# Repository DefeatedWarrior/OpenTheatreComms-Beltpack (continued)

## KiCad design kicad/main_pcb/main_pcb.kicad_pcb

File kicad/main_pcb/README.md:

# Beltpack main PCB, rev 0.1

The board behind the front shell: USB-C charging with a power path, the soft power switch and 3.3 V LDO, a fuel gauge,
the ESP32-S3 module, the LR2021 radio module with its antenna-diversity switch and two U.FL outputs, the NAU88C22 codec
with the XLR-4 headset and 3.5 mm TRRS outputs, an accelerometer, an IO expander, the three front buttons, the
flashlight LED, the vibration motor and the JST SH link to the top PCB.

| | |
|---|---|
| Size | 87.5 x 64.5 mm outline with the link tab, 1.6 mm FR4, 4 layers |
| Stack | F signal + GND pour, In1 signal + +3V3 pour, In2 solid GND plane, B signal + GND pour |
| Rules | 0.2 mm track and space, power and +3V3 0.4 mm, RF 0.35 mm, vias 0.6 / 0.3 mm, 0.5 mm copper to edge |
| Parts | 138 parts (59 on the front, 79 on the back; 21 of them unfitted options) plus 5 M2 holes. 0603 passives on hand-solder pads |
| DRC | 0 errors, 0 unconnected. 10 warnings, all expected: footprints adjusted from their library copies (silk moved off the board edge), the enclosure reference footprint has no library, and one pin-1 marker clipped by the mask |

## Files

| Path | Contents |
|---|---|
| `main_pcb.kicad_sch` | Schematic (one A1 sheet, a box per block) |
| `main_pcb.kicad_pcb` | Routed board. *Update PCB from Schematic* matches every footprint to its symbol |
| `main_pcb.kicad_dru` | Custom rules: single thermal spoke, the USB-C and power-switch pegs, the buttons by the tab edge |
| `lib/` | Project symbols and footprints (codec, charger, gauge, RF switch, LR2021 module, spring pin, coin motor) |
| `fab/main_pcb_gerbers.zip` | Gerbers (4 copper layers) + Excellon drill (PTH and NPTH), ready to upload |
| `fab/main_pcb_bom.csv` | BOM grouped by value, with part numbers and side. Unfitted parts are listed with quantity 0 |
| `fab/main_pcb_placement.csv` | Pick-and-place, mm (unfitted parts left out) |
| `fab/assembly.pdf` | Hand-assembly sheets, front and back (back drawn as seen from the back); unfitted parts in grey |
| `fab/main_pcb_schematic.pdf`, `fab/main_pcb_drc.rpt` | Schematic print and the DRC report |

Order as: 4 layers, 1.6 mm, JLC-style 7628 stack (or any 4-layer stack with about 0.2 mm from B to In2: the RF lines
were sized for that), HASL lead-free is fine for reflow (ENIG gives a flatter paste print on the QFN, TDFN and LGA, if you want the margin), any mask colour. The ESP32 and codec footprints have
0.2 mm thermal vias, so allow 0.2 mm drills.

## Circuit

**Power.** USB-C (5.1k CC pull-downs, so it asks for 5 V only) → USBLC6 ESD → TP4056 charger at about 800 mA (R3 = 1.5k;
2.4k gives 500 mA) with the pack NTC on CHG_TEMP (fit R5 instead if the pack has none). Power path: SS14 from VBUS to SYS,
AO3401A from the cell to SYS when USB is absent. TLV75733 (1 A) makes +3V3 from SYS.
Q1's drain is on the cell and its source on SYS. That's deliberate (the usual orientation for a charger with load
sharing): its body diode can only conduct from the cell to SYS, so with USB in, SYS can never charge the cell around the
charger. Don't swap it to source-on-battery: the body diode would then charge the cell straight from USB, with no
current limit, temperature check or end of charge.
Soft power: the side button pulls the LDO enable high through D2; the firmware then holds it with PWR_HOLD (IO17) through
D3, reads the button through Q2 (expander P03), and lets go of PWR_HOLD to switch off. MAX17048 gauge on the cell (0x36).
The pack connects through three spring pins: J8 battery +, J9 NTC, J10 battery −. J11, a JST XH 2-pin on the front above
the spring pins (pin 1 +, marked), is a second battery input in parallel with J8/J10, for a wired cell or bench supply.
A cell on J11 has no NTC: fit R5 to turn the charger's temperature check off.
**Dock:** J12, a vertical JST SH 4-pin (BM04B) on the back face at the bottom edge (x 25.5, y −33.25), sits wholly below the
battery pack (its body ends at y −31.3, the pack's underside is y −31), so its plug points backward into the 5 mm strip under
the pack. A flat cable runs from it to the dock contact board in the case bottom: pin 1 dock VBUS, 2 D−, 3 D+, 4 GND. Dock
VBUS feeds the pack's VBUS through D12 (B5819W), which also keeps the USB-C's 5 V off the exposed contacts; D+/D− join the
USB-C's data lines (full speed; about 46 mm of extra track on D+, 20 mm on D−). TP3 (BAT) gave way to J12: probe BAT on J11.

**ESP32-S3** (WROOM-1-N8R8, antenna end over the no-copper strip on the left):

| GPIO | Use | GPIO | Use |
|---|---|---|---|
| IO0 | Boot (test pad) | IO15 | I2S MCLK |
| IO1 | Jack sense | IO16 | Expander INT (shared with the top PCB) |
| IO4 / IO5 / IO6 / IO7 | I2S BCLK / FS / DOUT / DIN | IO17 | PWR_HOLD |
| IO8 / IO9 | I2C SDA / SCL | IO18 | Vibration motor |
| IO10 / IO11 / IO12 / IO13 | LR2021 NSS / MOSI / SCK / MISO | IO19 / IO20 | USB D− / D+ (native USB: flashing and serial) |
| IO14 | LR2021 BUSY | IO21 | LR2021 DIO6 (IRQ) |
| IO38 / IO39 | Left dial A / B | IO40 / IO41 | Right dial A / B |
| IO42 | Flashlight | IO47 | LR2021 NRESET |
| IO48 | Antenna switch | RXD0 / TXD0 | UART test pads |

**IO expander** (TCA9555 at 0x21; the top PCB's is at 0x20): P00 Back, P01 Function, P02 Menu, P03 power button,
P04 charging, P05 charge done, P06 USB present, P07 accelerometer INT1, P10 gauge alert, P11 LR2021 DIO5,
P12 LR2021 TX/RX enable, P13 accelerometer INT2.

**I2C bus**: codec 0x1A, accelerometer (LIS3DH) 0x18, gauge 0x36, main expander 0x21, top expander 0x20, OLED 0x3D, top LED driver (LP5024) 0x28 (it also answers 0x3C, its broadcast address).
The pull-ups are on the top PCB; R39 to R41 here are unfitted (fit them only to run this board without the top PCB).

**Radio.** LR2021 module (915 to 928 MHz port) → pi match (C14, L1, C15: 0 ohm and two unfitted shunts until tuned) →
100 pF DC block → PE4259 switch (IO48 high = antenna A) → 100 pF DC blocks → U.FL J5 (antenna A) and J6 (antenna B).
The 2.4 GHz port has a footprint-only match (L2, C20) and U.FL (J7), all unfitted in v1.

**Audio.** NAU88C22 in 2-wire mode. XLR-4 headset (Clear-Com wiring: 1 mic common, 2 mic +, 3 earpiece −, 4 earpiece +,
5 shell) on wire pads J3: dynamic mic into the left mic input, earpiece on the speaker (BTL) outputs. For headsets with
pin 3 tied to pin 1, swap R27 for a 100 uF 1206, remove R28 and fit R29. The unfitted OPA365 preamp (gain 22, 27 dB)
goes between the XLR mic and the codec: fit U9, C31 to C34 and R21 to R26, and remove R20.
3.5 mm TRRS (CTIA) on J2: stereo headphone out through 100 uF, electret mic into the right mic input with 2.2k bias,
jack sense on IO1.

**Other.** LIS3DH accelerometer, three PTS815 front buttons, 3 mm white flashlight LED (about 20 mA from SYS),
coin vibration motor, all ESD-protected where they leave the board. J4 (JST SH 10, mouth up on the tab) has the
same pinout as the top PCB's J1, for a straight pin-1-to-pin-1 cable.

## Check before ordering

1. **LR2021 module footprint: checked.** It now matches Elecrow's own design file for the module: pin 1 at the top of the
   left side seen from the top, numbered anticlockwise, 5 castellated pads per side at 1.27 mm, and four 1.2 mm ground
   pads underneath (each with a via). Every pin's function was checked against that file's nets.
2. **Radio supply link.** The module already has its own ferrite on its supply pin, so FB2 is fitted as a 0 ohm link.
   Its 0603 pads take a 120 ohm bead (BLM18PG121SN1D) if the radio ever needs a quieter supply.
3. **Codec routing.** The codec's support parts now sit beside the vias of the pins they serve: VREF is 5 mm of track,
   each mic pair 5 to 8 mm, the speaker pair 5 to 13 mm, the analog supply 21 mm. The lines to the 3.5 mm jack (headphones,
   mic, mic bias) are 20 to 65 mm because the jack is at the other end of the board.
4. **In1 carries signals too.** About 0.6 m of signal tracks run on In1; the +3V3 pour fills round them, and +3V3 is
   also routed as a net, so it's connected even where the pour is cut. In2 is an unbroken ground plane under everything.
5. **Codec: checked against the NAU88C22 datasheet (Rev 2.2).** MODE low with SPIEN at its default selects 2-wire
   control at 0x1A (0011010), and CSB/GPIO1 to ground follows the "unused digital inputs to ground" note. Following its
   application circuit, MICBIAS now has 4.7 uF (C28) and VDDC/VDDB a 4.7 uF bulk cap (C23) next to the 0.1 uF.
   Its example also puts 220 ohm series resistors on the I2S and I2C lines; this board has none, so add them in rev 0.2
   if the digital lines ring.
6. **Spring pins.** J8 to J10 have 1.0 mm holes for Xinyangze YZ08415060P-02 pins (LCSC C7471674): 0.8 mm tail, 4.5 mm
   free height, 4.0 mm working height, 3.7 mm fully in. The pack pads should sit 4.0 mm from the board's back face (the
   case was drawn for 3.7 mm with Mill-Max pins, so the pack seat moves 0.3 mm in the case redesign). A Mill-Max 0906
   still fits the hole, loosely.
7. **Charge current.** R3 = 1.5k gives about 800 mA. A USB-C port without Power Delivery only promises 500 mA (USB 2.0) or
   900 mA (USB 3.x); 2.4k gives 500 mA if you ever need it.
8. **RF.** The 915 MHz pi match ships as 0 ohm with both shunts unfitted: tune C14, L1, C15 with a VNA. The PE4259 runs at
   3.3 V, its rated maximum supply.
9. **Fit check.** Every part's box was checked against the case model: only the 3.5 mm jack and the flashlight LED reach
   into the front shell, through their openings as intended. The case's power button now has a 0.37 mm nub to reach the
   Alps switch's plunger (updated case files in `beltpack_case`).

## Rebuilding

Everything here is generated from `pcb_main/design.py`. See `pcb_main/README.md` for the build steps. After the scripted
build, one connection needed help: R7 (the LDO enable pull-down) was moved with `movepart.py R7 --free` and its enable
line routed by `maze.py`.
Edit the board by hand in KiCad if you prefer; just don't rerun the scripts afterwards, or they'll overwrite your edits.

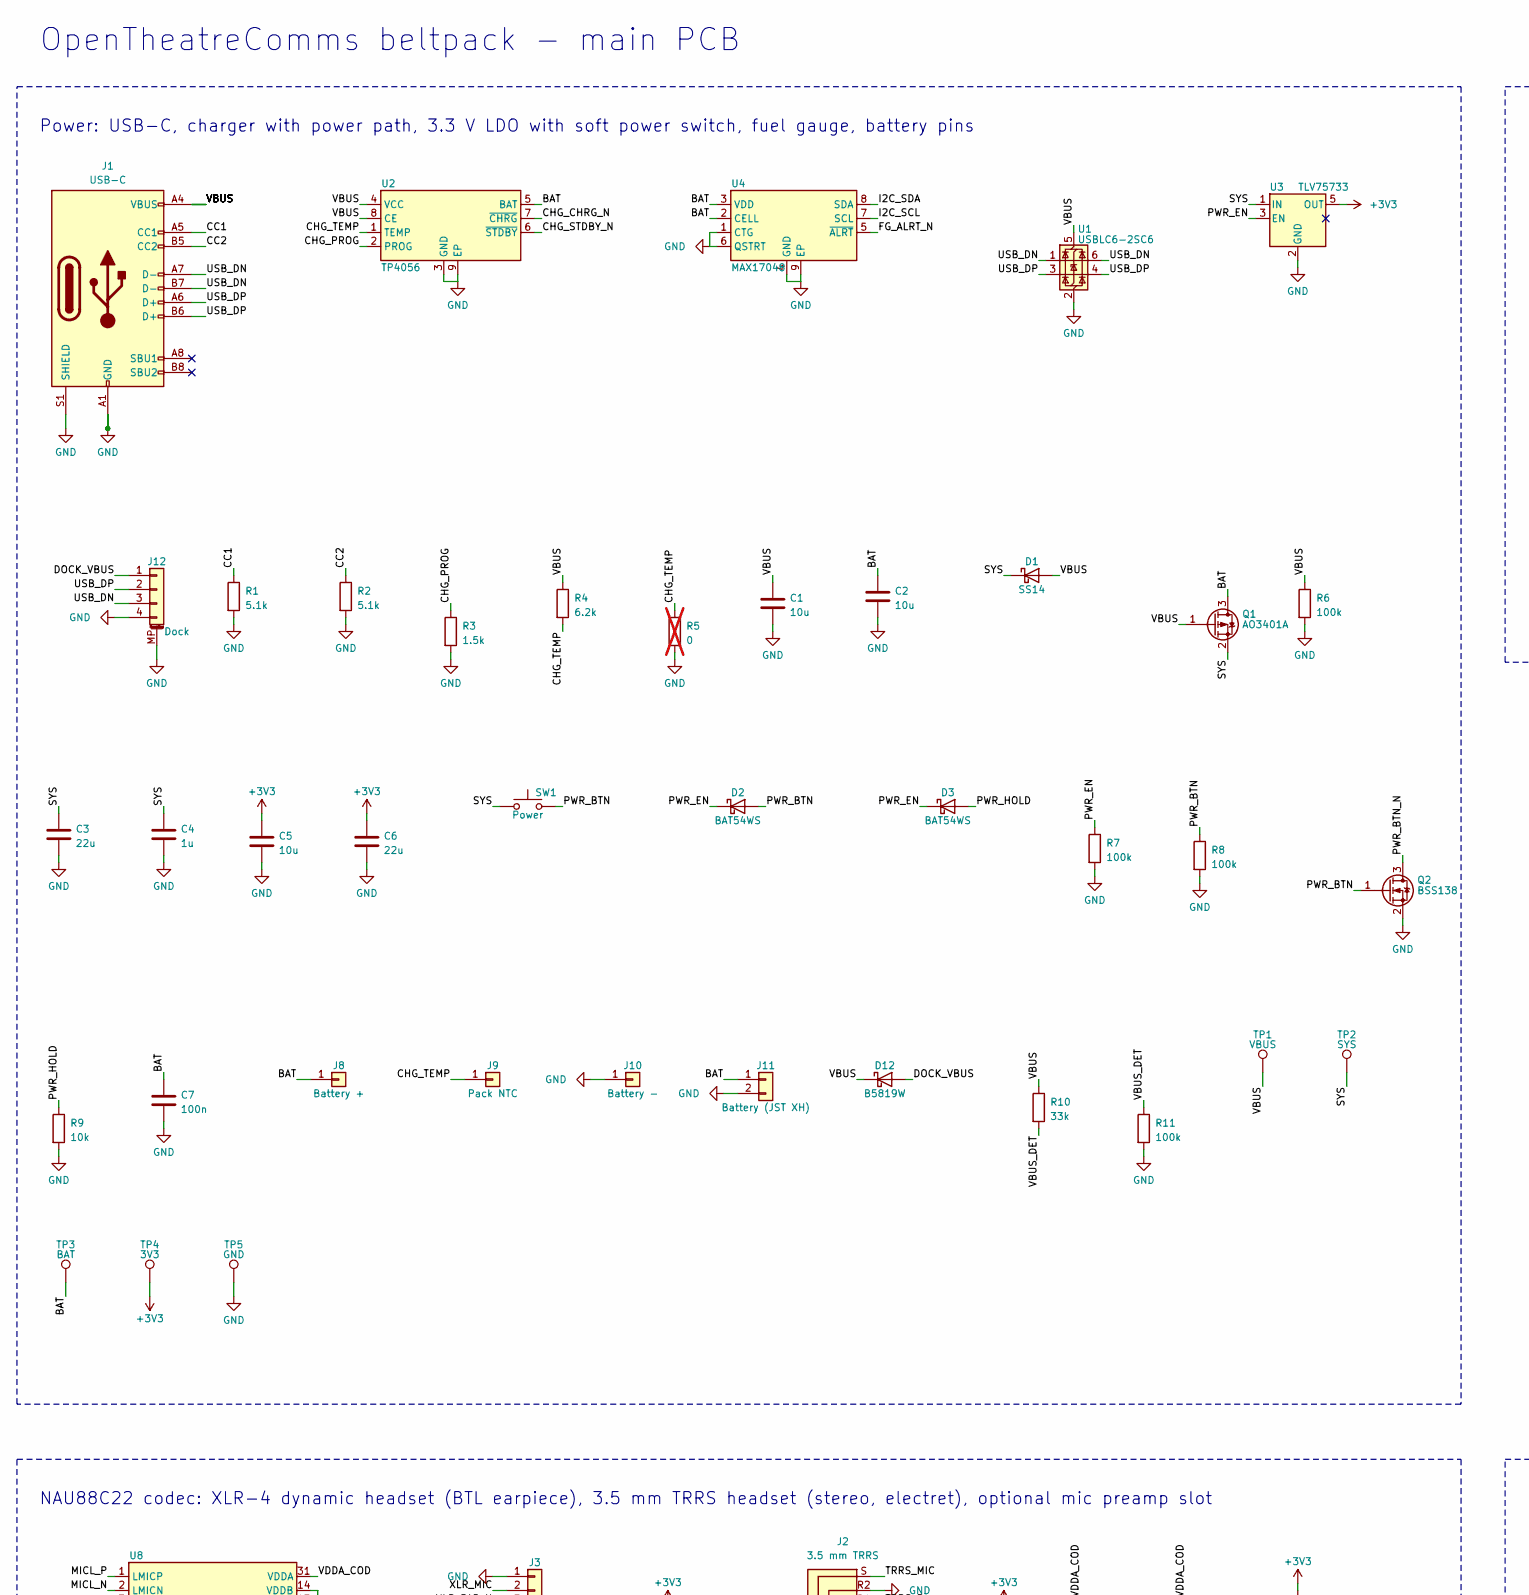
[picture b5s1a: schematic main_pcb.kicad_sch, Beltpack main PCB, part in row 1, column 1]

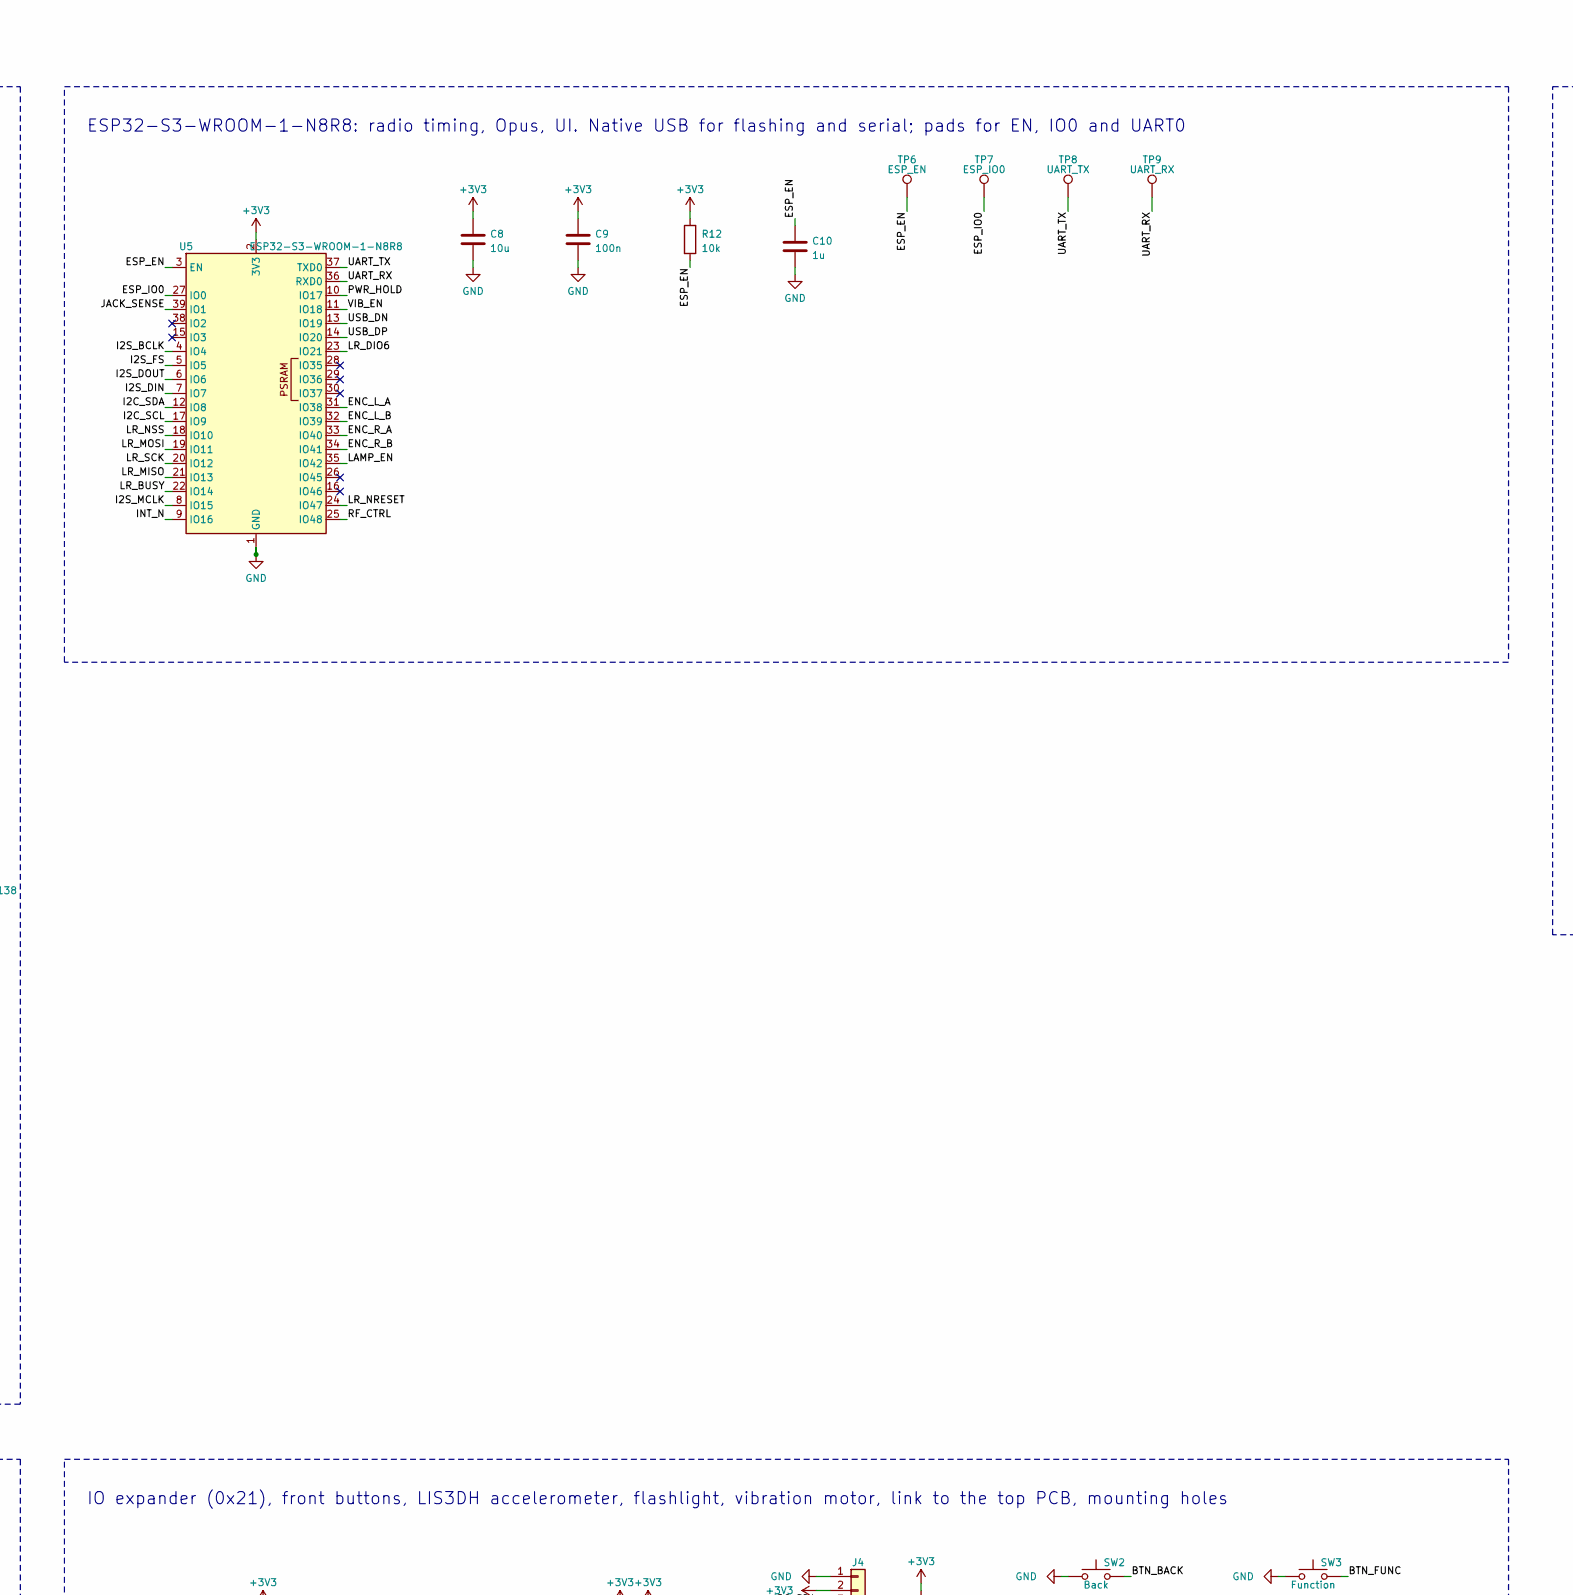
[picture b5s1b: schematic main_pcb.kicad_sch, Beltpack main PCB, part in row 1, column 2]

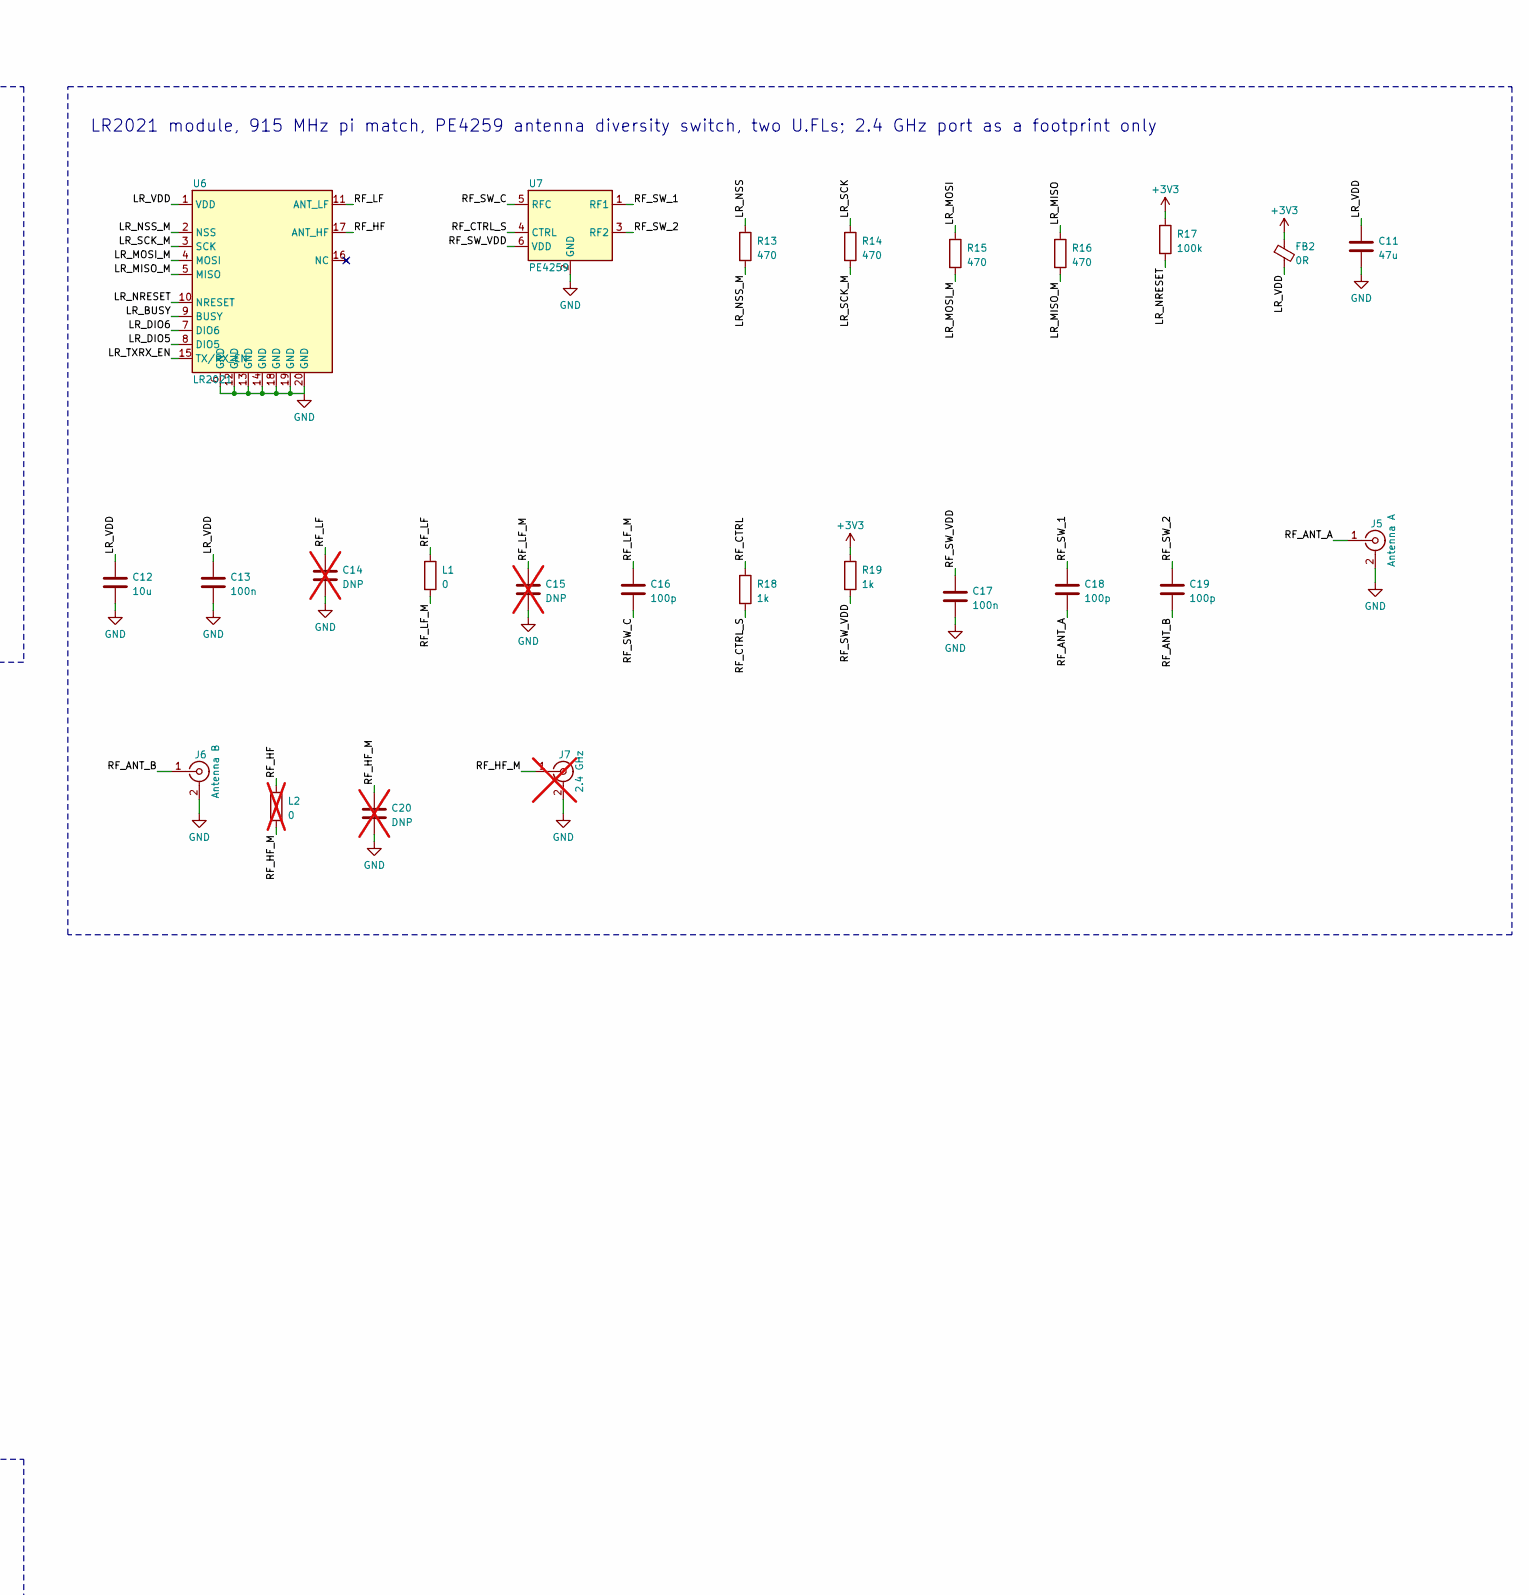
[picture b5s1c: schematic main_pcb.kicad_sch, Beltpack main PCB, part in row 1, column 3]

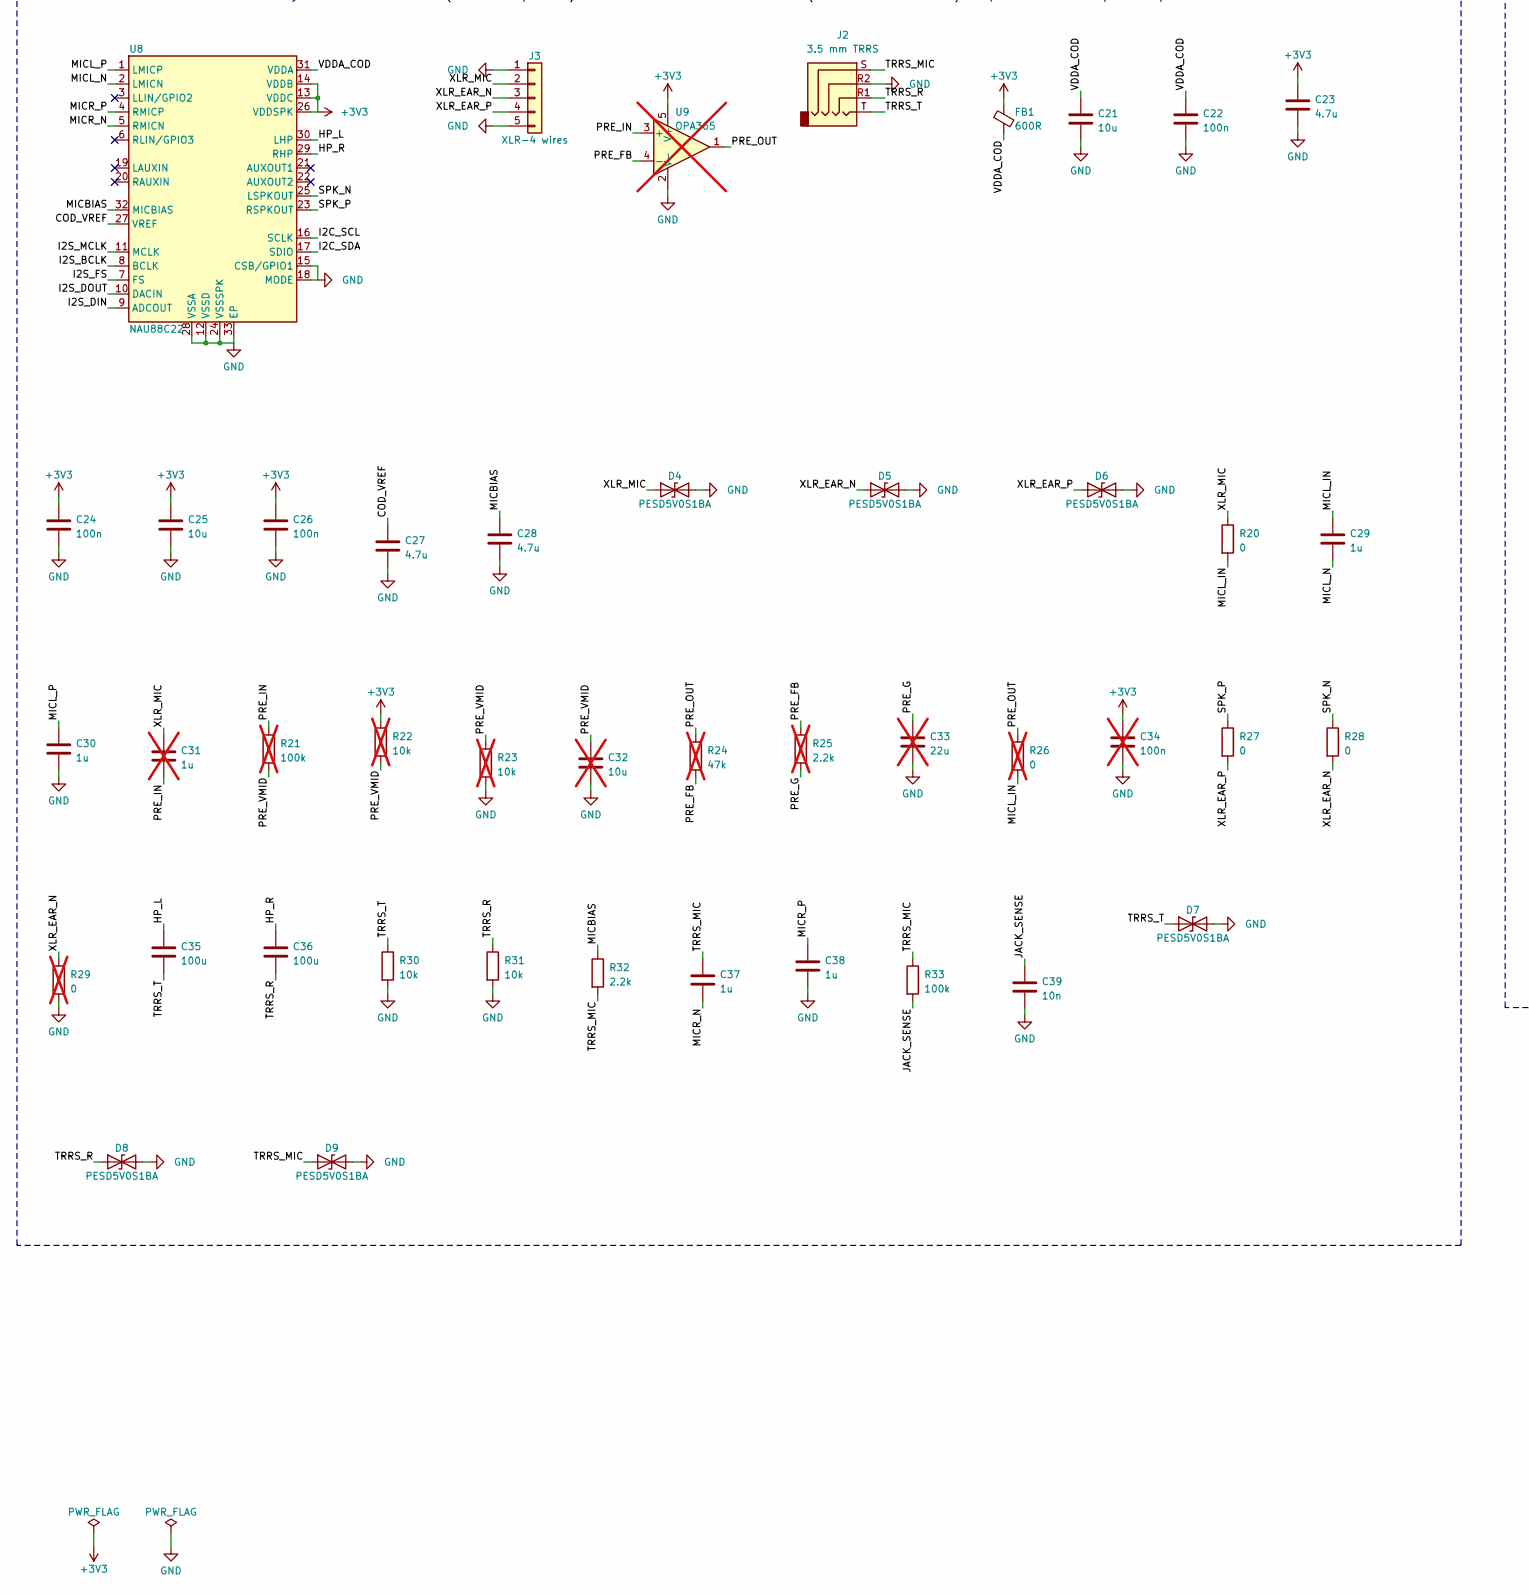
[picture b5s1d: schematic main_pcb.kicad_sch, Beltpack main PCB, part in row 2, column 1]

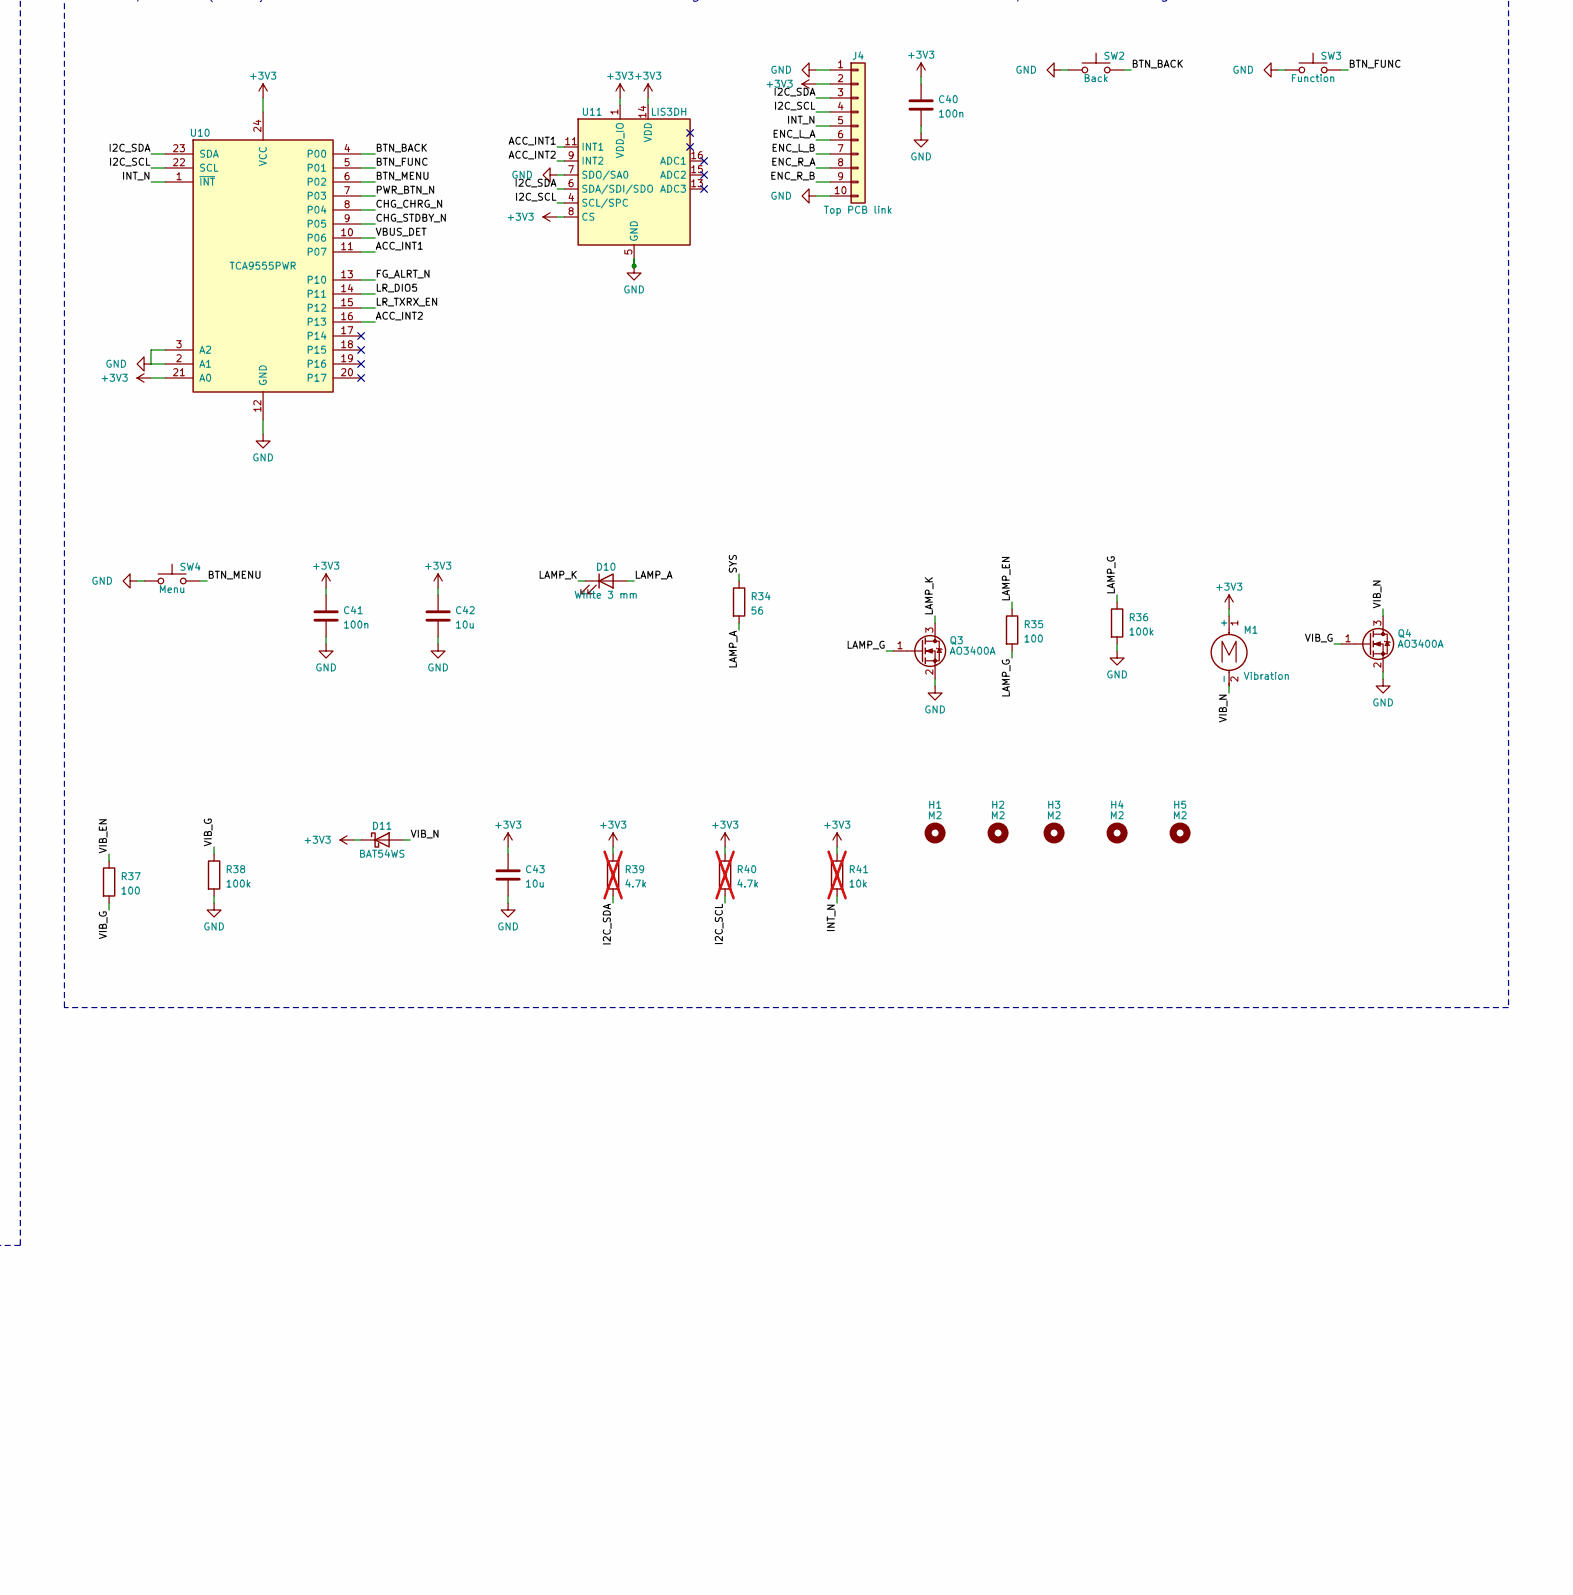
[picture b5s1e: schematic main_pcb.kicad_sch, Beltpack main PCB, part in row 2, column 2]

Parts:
C1, C2, C5, C8, C12, C21, C25, C42, C43: 10u; C_0603_1608Metric_Pad1.08x0.95mm_HandSolder; MPN 0603 X5R 10 V
C3, C6: 22u; C_1206_3216Metric_Pad1.33x1.80mm_HandSolder; MPN 1206 X5R 10 V
C4, C10, C29, C30, C37, C38: 1u; C_0603_1608Metric_Pad1.08x0.95mm_HandSolder; MPN 0603 X5R 10 V
C7, C9, C13, C17, C22, C24, C26, C40, C41: 100n; C_0603_1608Metric_Pad1.08x0.95mm_HandSolder; MPN 0603 X7R
C11: 47u; C_1206_3216Metric_Pad1.33x1.80mm_HandSolder; MPN 1206 X5R 6.3 V
C14, C15, C20: DNP; C_0603_1608Metric_Pad1.08x0.95mm_HandSolder; MPN 0603 C0G, tune; not fitted
C16, C18, C19: 100p; C_0603_1608Metric_Pad1.08x0.95mm_HandSolder; MPN 0603 C0G 50 V
C23, C27, C28: 4.7u; C_0603_1608Metric_Pad1.08x0.95mm_HandSolder; MPN 0603 X5R 10 V
C31: 1u; C_0603_1608Metric_Pad1.08x0.95mm_HandSolder; MPN 0603 X5R 10 V; not fitted
C32: 10u; C_0603_1608Metric_Pad1.08x0.95mm_HandSolder; MPN 0603 X5R 10 V; not fitted
C33: 22u; C_1206_3216Metric_Pad1.33x1.80mm_HandSolder; MPN 1206 X5R 6.3 V; not fitted
C34: 100n; C_0603_1608Metric_Pad1.08x0.95mm_HandSolder; MPN 0603 X7R; not fitted
C35, C36: 100u; C_1206_3216Metric_Pad1.33x1.80mm_HandSolder; MPN 1206 X5R 6.3 V
C39: 10n; C_0603_1608Metric_Pad1.08x0.95mm_HandSolder; MPN 0603 X7R
D1: SS14; D_SMA; MPN SS14 (SMA)
D2, D3, D11: BAT54WS; D_SOD-323_HandSoldering; MPN Diodes BAT54WS
D4, D5, D6, D7, D8, D9: PESD5V0S1BA; D_SOD-323_HandSoldering; MPN Nexperia PESD5V0S1BA
D10: White 3 mm; LED_D3.0mm_Horizontal_O1.27mm_Z2.0mm; MPN 3 mm white LED, 20 mA
D12: B5819W; D_SOD-123; MPN B5819W (SOD-123)
FB1: 600R; L_0603_1608Metric_Pad1.05x0.95mm_HandSolder; MPN Murata BLM18PG601SN1D
FB2: 0R; L_0603_1608Metric_Pad1.05x0.95mm_HandSolder; MPN 0603 0R (or Murata BLM18PG121SN1D)
H1, H2, H3, H4, H5: M2; MountingHole_2.2mm_M2
J1: USB-C; USB_C_Receptacle_GCT_USB4105-xx-A_16P_TopMnt_Horizontal; MPN GCT USB4105-GF-A
J2: 3.5 mm TRRS; Jack_3.5mm_PJ320D_Horizontal; MPN PJ-320D
J3: XLR-4 wires; PinHeader_1x05_P2.54mm_Vertical; MPN Neutrik NC4MD-L-1 (wired)
J4: Top PCB link; JST_SH_SM10B-SRSS-TB_1x10-1MP_P1.00mm_Horizontal; MPN JST SM10B-SRSS-TB
J5: Antenna A; U.FL_Hirose_U.FL-R-SMT-1_Vertical; MPN Hirose U.FL-R-SMT-1(10)
J6: Antenna B; U.FL_Hirose_U.FL-R-SMT-1_Vertical; MPN Hirose U.FL-R-SMT-1(10)
J7: 2.4 GHz; U.FL_Hirose_U.FL-R-SMT-1_Vertical; MPN Hirose U.FL-R-SMT-1(10); not fitted
J8: Battery +; MillMax_0906_SpringPin; MPN Xinyangze YZ08415060P-02
J9: Pack NTC; MillMax_0906_SpringPin; MPN Xinyangze YZ08415060P-02
J10: Battery -; MillMax_0906_SpringPin; MPN Xinyangze YZ08415060P-02
J11: Battery (JST XH); JST_XH_B2B-XH-A_1x02_P2.50mm_Vertical; MPN JST B2B-XH-A(LF)(SN)
J12: Dock; JST_SH_SM04B-SRSS-TB_1x04-1MP_P1.00mm_Horizontal; MPN JST SM04B-SRSS-TB(LF)(SN)
L1: 0; R_0603_1608Metric_Pad0.98x0.95mm_HandSolder; MPN 0603 0R or RF inductor
L2: 0; R_0603_1608Metric_Pad0.98x0.95mm_HandSolder; MPN 0603 0R or RF inductor; not fitted
M1: Vibration; Motor_Coin_8mm_LeadPads; MPN 8 x 2.7 mm coin vibration motor, 3 V
Q1: AO3401A; SOT-23; MPN AOS AO3401A
Q2: BSS138; SOT-23; MPN onsemi BSS138
Q3, Q4: AO3400A; SOT-23; MPN AOS AO3400A
R1, R2: 5.1k; R_0603_1608Metric_Pad0.98x0.95mm_HandSolder; MPN 0603 1%
R3: 1.5k; R_0603_1608Metric_Pad0.98x0.95mm_HandSolder; MPN 0603 1%
R4: 6.2k; R_0603_1608Metric_Pad0.98x0.95mm_HandSolder; MPN 0603 1%
R5, R26, R29: 0; R_0603_1608Metric_Pad0.98x0.95mm_HandSolder; MPN 0603 1%; not fitted
R6, R7, R8, R11, R17, R33, R36, R38: 100k; R_0603_1608Metric_Pad0.98x0.95mm_HandSolder; MPN 0603 1%
R9, R12, R30, R31: 10k; R_0603_1608Metric_Pad0.98x0.95mm_HandSolder; MPN 0603 1%
R10: 33k; R_0603_1608Metric_Pad0.98x0.95mm_HandSolder; MPN 0603 1%
R13, R14, R15, R16: 470; R_0603_1608Metric_Pad0.98x0.95mm_HandSolder; MPN 0603 1%
R18, R19: 1k; R_0603_1608Metric_Pad0.98x0.95mm_HandSolder; MPN 0603 1%
R20, R28: 0; R_0603_1608Metric_Pad0.98x0.95mm_HandSolder; MPN 0603 1%
R21: 100k; R_0603_1608Metric_Pad0.98x0.95mm_HandSolder; MPN 0603 1%; not fitted
R22, R23, R41: 10k; R_0603_1608Metric_Pad0.98x0.95mm_HandSolder; MPN 0603 1%; not fitted
R24: 47k; R_0603_1608Metric_Pad0.98x0.95mm_HandSolder; MPN 0603 1%; not fitted
R25: 2.2k; R_0603_1608Metric_Pad0.98x0.95mm_HandSolder; MPN 0603 1%; not fitted
R27: 0; R_1206_3216Metric_Pad1.30x1.75mm_HandSolder; MPN 1206 0R
R32: 2.2k; R_0603_1608Metric_Pad0.98x0.95mm_HandSolder; MPN 0603 1%
R34: 56; R_0603_1608Metric_Pad0.98x0.95mm_HandSolder; MPN 0603 1%
R35, R37: 100; R_0603_1608Metric_Pad0.98x0.95mm_HandSolder; MPN 0603 1%
R39, R40: 4.7k; R_0603_1608Metric_Pad0.98x0.95mm_HandSolder; MPN 0603 1%; not fitted
SW1: Power; SW_Push_1P1T-MP_NO_Horizontal_Alps_SKRTLAE010; MPN Alps SKRTLAE010
SW2: Back; SW_SPST_PTS810; MPN C&K PTS815 SJM 250 SMTR LFS
SW3: Function; SW_SPST_PTS810; MPN C&K PTS815 SJM 250 SMTR LFS
SW4: Menu; SW_SPST_PTS810; MPN C&K PTS815 SJM 250 SMTR LFS
TP1: VBUS; TestPoint_Pad_D1.0mm
TP2: SYS; TestPoint_Pad_D1.0mm
TP3: BAT; TestPoint_Pad_D1.0mm
TP4: 3V3; TestPoint_Pad_D1.0mm
TP5: GND; TestPoint_Pad_D1.0mm
TP6: ESP_EN; TestPoint_Pad_D1.0mm
TP7: ESP_IO0; TestPoint_Pad_D1.0mm
TP8: UART_TX; TestPoint_Pad_D1.0mm
TP9: UART_RX; TestPoint_Pad_D1.0mm
U1: USBLC6-2SC6; SOT-23-6; MPN ST USBLC6-2SC6
U2: TP4056; SOIC-8-1EP_3.9x4.9mm_P1.27mm_EP2.29x3mm_ThermalVias; MPN TOPPOWER TP4056 (ESOP-8)
U3: TLV75733; SOT-23-5; MPN TI TLV75733PDBVR
U4: MAX17048; TDFN-8-1EP_2x2mm_P0.5mm_EP0.8x1.2mm; MPN Analog MAX17048G+T10
U5: ESP32-S3-WROOM-1-N8R8; ESP32-S3-WROOM-1; MPN Espressif ESP32-S3-WROOM-1-N8R8
U6: LR2021; LR2021_Elecrow_10x10mm; MPN Elecrow LR2021 module (LMM16121D)
U7: PE4259; SOT-363_SC-70-6; MPN pSemi PE4259-63
U8: NAU88C22; QFN-32-1EP_5x5mm_P0.5mm_EP3.45x3.45mm_ThermalVias; MPN Nuvoton NAU88C22YG
U9: OPA365; SOT-23-5; MPN TI OPA365AIDBVR; not fitted
U10: TCA9555PWR; TSSOP-24_4.4x7.8mm_P0.65mm; MPN TI TCA9555PWR
U11: LIS3DH; LGA-16_3x3mm_P0.5mm; MPN ST LIS3DHTR

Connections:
+3V3: C5.1, C6.1, C8.1, C9.1, C23.1, C24.1, C25.1, C26.1, C34.1, C40.1, C41.1, C42.1, C43.1, D11.1 (K), FB1.1, FB2.1, J4.2, M1.1 (+), R12.1, R17.1, R19.1, R22.1, R39.1, R40.1, R41.1, TP4.1, U3.5 (OUT), U5.2 (3V3), U8.13 (VDDC), U8.14 (VDDB), U8.26 (VDDSPK), U9.5 (V+), U10.21 (A0), U10.24 (VCC), U11.1 (VDD_IO), U11.8 (CS), U11.14 (VDD)
/ACC_INT1: U10.11 (P07), U11.11 (INT1)
/ACC_INT2: U10.16 (P13), U11.9 (INT2)
/BAT: C2.1, C7.1, J8.1, J11.1, Q1.3 (D), TP3.1, U2.5 (BAT), U4.2 (CELL), U4.3 (VDD)
/BTN_BACK: SW2.2, U10.4 (P00)
/BTN_FUNC: SW3.2, U10.5 (P01)
/BTN_MENU: SW4.2, U10.6 (P02)
/CC1: J1.A5 (CC1), R1.1
/CC2: J1.B5 (CC2), R2.1
/CHG_CHRG_N: U2.7 (~CHRG), U10.8 (P04)
/CHG_PROG: R3.1, U2.2 (PROG)
/CHG_STDBY_N: U2.6 (~STDBY), U10.9 (P05)
/CHG_TEMP: J9.1, R4.2, R5.1, U2.1 (TEMP)
/COD_VREF: C27.1, U8.27 (VREF)
/DOCK_VBUS: D12.2 (A), J12.1
/ENC_L_A: J4.6, U5.31 (IO38)
/ENC_L_B: J4.7, U5.32 (IO39)
/ENC_R_A: J4.8, U5.33 (IO40)
/ENC_R_B: J4.9, U5.34 (IO41)
/ESP_EN: C10.1, R12.2, TP6.1, U5.3 (EN)
/ESP_IO0: TP7.1, U5.27 (IO0)
/FG_ALRT_N: U4.5 (~ALRT), U10.13 (P10)
/HP_L: C35.1, U8.30 (LHP)
/HP_R: C36.1, U8.29 (RHP)
/I2C_SCL: J4.4, R40.2, U4.7 (SCL), U5.17 (IO9), U8.16 (SCLK), U10.22 (SCL), U11.4 (SCL/SPC)
/I2C_SDA: J4.3, R39.2, U4.8 (SDA), U5.12 (IO8), U8.17 (SDIO), U10.23 (SDA), U11.6 (SDA/SDI/SDO)
/I2S_BCLK: U5.4 (IO4), U8.8 (BCLK)
/I2S_DIN: U5.7 (IO7), U8.9 (ADCOUT)
/I2S_DOUT: U5.6 (IO6), U8.10 (DACIN)
/I2S_FS: U5.5 (IO5), U8.7 (FS)
/I2S_MCLK: U5.8 (IO15), U8.11 (MCLK)
/INT_N: J4.5, R41.2, U5.9 (IO16), U10.1 (~INT)
/JACK_SENSE: C39.1, R33.2, U5.39 (IO1)
/LAMP_A: D10.2 (A), R34.2
/LAMP_EN: R35.1, U5.35 (IO42)
/LAMP_G: Q3.1 (G), R35.2, R36.1
/LAMP_K: D10.1 (K), Q3.3 (D)
/LR_BUSY: U5.22 (IO14), U6.9 (BUSY)
/LR_DIO5: U6.8 (DIO5), U10.14 (P11)
/LR_DIO6: U5.23 (IO21), U6.7 (DIO6)
/LR_MISO: R16.1, U5.21 (IO13)
/LR_MISO_M: R16.2, U6.5 (MISO)
/LR_MOSI: R15.1, U5.19 (IO11)
/LR_MOSI_M: R15.2, U6.4 (MOSI)
/LR_NRESET: R17.2, U5.24 (IO47), U6.10 (NRESET)
/LR_NSS: R13.1, U5.18 (IO10)
/LR_NSS_M: R13.2, U6.2 (NSS)
/LR_SCK: R14.1, U5.20 (IO12)
/LR_SCK_M: R14.2, U6.3 (SCK)
/LR_TXRX_EN: U6.15 (TX/RX_EN), U10.15 (P12)
/LR_VDD: C11.1, C12.1, C13.1, FB2.2, U6.1 (VDD)
/MICBIAS: C28.1, R32.1, U8.32 (MICBIAS)
/MICL_IN: C29.1, R20.2, R26.2
/MICL_N: C29.2, U8.2 (LMICN)
/MICL_P: C30.1, U8.1 (LMICP)
/MICR_N: C37.2, U8.5 (RMICN)
/MICR_P: C38.1, U8.4 (RMICP)
/PRE_FB: R24.2, R25.1, U9.4 (-)
/PRE_G: C33.1, R25.2
/PRE_IN: C31.2, R21.1, U9.3 (+)
/PRE_OUT: R24.1, R26.1, U9.1
/PRE_VMID: C32.1, R21.2, R22.2, R23.1
/PWR_BTN: D2.2 (A), Q2.1 (G), R8.1, SW1.2
/PWR_BTN_N: Q2.3 (D), U10.7 (P03)
/PWR_EN: D2.1 (K), D3.1 (K), R7.1, U3.3 (EN)
/PWR_HOLD: D3.2 (A), R9.1, U5.10 (IO17)
/RF_ANT_A: C18.2, J5.1 (In)
/RF_ANT_B: C19.2, J6.1 (In)
/RF_CTRL: R18.1, U5.25 (IO48)
/RF_CTRL_S: R18.2, U7.4 (CTRL)
/RF_HF: L2.1, U6.17 (ANT_HF)
/RF_HF_M: C20.1, J7.1 (In), L2.2
/RF_LF: C14.1, L1.1, U6.11 (ANT_LF)
/RF_LF_M: C15.1, C16.1, L1.2
/RF_SW_1: C18.1, U7.1 (RF1)
/RF_SW_2: C19.1, U7.3 (RF2)
/RF_SW_C: C16.2, U7.5 (RFC)
/RF_SW_VDD: C17.1, R19.2, U7.6 (VDD)
/SPK_N: R28.1, U8.25 (LSPKOUT)
/SPK_P: R27.1, U8.23 (RSPKOUT)
/SYS: C3.1, C4.1, D1.1 (K), Q1.2 (S), R34.1, SW1.1, TP2.1, U3.1 (IN)
/TRRS_MIC: C37.1, D9.1 (A1), J2.S, R32.2, R33.1
/TRRS_R: C36.2, D8.1 (A1), J2.R1, R31.1
/TRRS_T: C35.2, D7.1 (A1), J2.T, R30.1
/UART_RX: TP9.1, U5.36 (RXD0)
/UART_TX: TP8.1, U5.37 (TXD0)
/VBUS: C1.1, D1.2 (A), D12.1 (K), J1.A4 (VBUS), J1.A9 (VBUS), J1.B4 (VBUS), J1.B9 (VBUS), Q1.1 (G), R4.1, R6.1, R10.1, TP1.1, U1.5 (VBUS), U2.4 (VCC), U2.8 (CE)
/VBUS_DET: R10.2, R11.1, U10.10 (P06)
/VDDA_COD: C21.1, C22.1, FB1.2, U8.31 (VDDA)
/VIB_EN: R37.1, U5.11 (IO18)
/VIB_G: Q4.1 (G), R37.2, R38.1
/VIB_N: D11.2 (A), M1.2 (-), Q4.3 (D)
/XLR_EAR_N: D5.1 (A1), J3.3, R28.2, R29.1
/XLR_EAR_P: D6.1 (A1), J3.4, R27.2
/XLR_MIC: C31.1, D4.1 (A1), J3.2, R20.1
GND: C1.2, C2.2, C3.2, C4.2, C5.2, C6.2, C7.2, C8.2, C9.2, C10.2, C11.2, C12.2, C13.2, C14.2, C15.2, C17.2, C20.2, C21.2, C22.2, C23.2, C24.2, C25.2, C26.2, C27.2, C28.2, C30.2, C32.2, C33.2, C34.2, C38.2, C39.2, C40.2, C41.2, C42.2, C43.2, D4.2 (A2), D5.2 (A2), D6.2 (A2), D7.2 (A2), D8.2 (A2), D9.2 (A2), J1.A1 (GND), J1.A12 (GND), J1.B1 (GND), J1.B12 (GND), J1.S1 (SHIELD), J2.R2, J3.1, J3.5, J4.1, J4.10, J5.2 (Ext), J6.2 (Ext), J7.2 (Ext), J10.1, J11.2, J12.4, J12.MP (MountPin), Q2.2 (S), Q3.2 (S), Q4.2 (S), R1.2, R2.2, R3.2, R5.2, R6.2, R7.2, R8.2, R9.2, R11.2, R23.2, R29.2, R30.2, R31.2, R36.2, R38.2, SW2.1, SW3.1, SW4.1, TP5.1, U1.2 (GND), U2.3 (GND), U2.9 (EP), U3.2 (GND), U4.1 (CTG), U4.4 (GND), U4.6 (QSTRT), U4.9 (EP), U5.1 (GND), U5.40 (GND), U5.41 (GND), U6.6 (GND), U6.12 (GND), U6.13 (GND), U6.14 (GND), U6.18 (GND), U6.19 (GND), U6.20 (GND), U7.2 (GND), U8.12 (VSSD), U8.15 (CSB/GPIO1), U8.18 (MODE), U8.24 (VSSSPK), U8.28 (VSSA), U8.33 (EP), U9.2 (V-), U10.2 (A1), U10.3 (A2), U10.12 (GND), U11.5 (GND), U11.7 (SDO/SA0), U11.10 (GND), U11.12 (GND)

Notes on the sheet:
Power: USB-C, charger with power path, 3.3 V LDO with soft power switch, fuel gauge, battery pins
ESP32-S3-WROOM-1-N8R8: radio timing, Opus, UI. Native USB for flashing and serial; pads for EN, IO0 and UART0
LR2021 module, 915 MHz pi match, PE4259 antenna diversity switch, two U.FLs; 2.4 GHz port as a footprint only
NAU88C22 codec: XLR-4 dynamic headset (BTL earpiece), 3.5 mm TRRS headset (stereo, electret), optional mic preamp slot
IO expander (0x21), front buttons, LIS3DH accelerometer, flashlight, vibration motor, link to the top PCB, mounting holes
OpenTheatreComms beltpack - main PCB

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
